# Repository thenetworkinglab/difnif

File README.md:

# DifNif: DBA-ESDI Solid State Drive Emulator

DifNif is a drive emulator that replaces an IBM DBA-ESDI hard drive. 
It was designed by Eric Schlaepfer ([schlae/difnif](https://github.com/schlae/difnif)),
with the project's initial release intended to replace the hard drive in 
IBM ThinkPad 700C laptops, also including an alpha version of a PS/2 desktop 
form-factor emulator.  This fork is an attempt to complete 
the development of the 72-pin board for PS/2 desktops; the changes are 
listed in [docs/formfactor-review.md](docs/formfactor-review.md).

And before you ask: the name 'DifNif' comes from DF9F, 
the Micro Channel adapter ID that IBM's DBA-ESDI drives report.

**Status:** the Rev P2 PS/2 board works in a PS/2 55SX and Model 70, with or
without a Teensy, booting DOS 6.22 and OS/2 1.1. Releases are listed in
[CHANGELOG.md](CHANGELOG.md).

## Background

IBM PS/2 computers from the late 1980s and early 1990s typically used a
disk interface called DBA-ESDI (Direct Bus Attach - Enhanced
Small Device Interface). A DBA-ESDI drive has its controller integrated
with the drive electronics, and sits directly on the Micro Channel
bus, more like an IDE drive, but with its own register interface.

These drives are becoming rare because many have failed mechanically or
been damaged by leaking capacitors. MCA SCSI cards are an alternative on some
machines, but are getting expensive and difficult to find as well and
aren't compatible with all PS/2s. Some PS/2s also need an IML (initial microcode load)
partition on their disk, and can only load it from a DBA-ESDI drive.

DifNif implements the DBA-ESDI interface in a Lattice iCE40 FPGA and keeps
the disk as an image file on an SD card. Eric's design pairs the FPGA with a
Teensy 4.1 microcontroller; this fork adds a build that runs a small RISC-V
processor inside the FPGA instead, so the board needs no Teensy.

## Status

The Rev P2 board for PS/2 desktops (this fork) can be built two ways from
the same board:

- **FPGA-only** (recommended): no Teensy; the SD card goes in the board's
  own socket. Release v2026.11.23-1.
- **With a Teensy 4.1**, Eric's arrangement, with this fork's fixes; the SD
  card goes in the Teensy. Firmware v2026.11.21-5 and FPGA v2026.11.21-1.

Both work in a PS/2 55SX and a Model 70: they're set up with the Reference
Diskette, boot DOS 6.22, and pass a copy test that checks every file written
(the FPGA-only build overnight in the Model 70: about 367 rounds, no errors).
OS/2 1.1 installs and boots with the Teensy build in both machines, and boots
with the FPGA-only build in the Model 70 (not yet tried in its 55SX). With
the FPGA-only build, switching the PS/2 off straight after a write loses
nothing.

Speed, measured with DiskMeter (random / sequential / buffered, KB/s) and
sunbench (raw BIOS reads and writes, 64 KB blocks, MB/s), in a Model 70
(8570-A21: 25 MHz 80386DX, 64 KB cache) and a 55SX (8555-061: 16 MHz
80386SX, no cache):

| | Model 70 | 55SX |
|---|---|---|
| FPGA-only, DiskMeter | 3555 / 3206 / 3213 | 2222 / 2241 / 2432 |
| FPGA-only, sunbench read / write | 2.99 / 2.50 | 2.13 / 1.87 |
| Teensy build, DiskMeter | 1942 / 2036 / 2010 | 2108 / 2266 / 2305 |
| Eric's original design, DiskMeter | about 990 | about 690 |
| McIDE (an IDE adapter), DiskMeter | 2477 / 2477 / 2477 | 1867 / 1876 / 2005 |

Not yet tested: the PS/2 50Z, and this fork's FPGA changes on the ThinkPad
board (Eric's ThinkPad board works with his original design, on the `main`
branch).

**Data loss:** this is a hobby project with no formal testing. Keep backup
copies of all disk images.

## Making a board

This needs surface-mount assembly (an assembly service will do it), a
computer with the open-source FPGA tools, and an FTDI FT232H adapter. These
steps are for the FPGA-only build; the Teensy build differs in steps 4 to 6
(see below).

1. **Order the board.** `pcb_formfactor/fab/` has the Gerber and drill files
   (`DifNifFormFactor-RevP2.zip`), a parts list and a placement file for an
   assembly service. Order it 1.6 mm thick, with gold fingers and a bevelled
   connector edge; [docs/formfactor-review.md](docs/formfactor-review.md),
   "Fab files", has the details. Fit the 2x4 header J2 yourself (for
   programming); the Teensy socket is only needed for the Teensy build.
2. **Print the sled.** [mech/difnif_PS2_drive_sled.STL](mech/difnif_PS2_drive_sled.STL)
   replaces the IBM drive's sled; the board screws into it.
3. **Install the tools:** yosys, nextpnr and icestorm (for example
   [oss-cad-suite](https://github.com/YosysHQ/oss-cad-suite-build)), and a
   RISC-V C compiler, `riscv64-elf-gcc` (for example from Homebrew).
4. **Build and program the FPGA.** In `verilog/`:

       make BOARD=ps2 CPU=1          # firmware and FPGA, into build/ps2-cpu/
       make prog BOARD=ps2 CPU=1     # writes the FPGA's flash through J2

   Wire the FT232H to J2:

   | J2 pin | Signal | FT232H pin |
   |---|---|---|
   | 1 | Flash chip select | AD4 |
   | 2 | CDONE | AD6 |
   | 3 | SCK | AD0 |
   | 4 | CRESET | AD7 |
   | 5 | Flash data out (CIPO) | AD2 |
   | 6 | GND | GND |
   | 7 | Flash data in (COPI) | AD1 |
   | 8 | +3.3 V (leave unconnected) | |

   The board must be powered while it's programmed: in a switched-on PS/2,
   or on the bench with 5 V on the Teensy socket's VIN pin (U13 pin 48).
5. **Make the disk image.** The drive is a file called `disk0.img`, a whole
   number of megabytes up to 1023 MB, in the root directory of a FAT32 or
   exFAT SD card. For 120 MB:

       dd if=/dev/zero of=disk0.img bs=1048576 count=120

   The file may be in up to 32 pieces on the card. The card goes in the
   board's socket, J3. [docs/sd-card.md](docs/sd-card.md) has the steps for
   putting an image on a card (erase it, then copy, so the image is in one
   piece) and what the log means if the board can't use it.
6. **Optional: the serial log.** The board reports what it found on the card
   (and why, if it can't use the image) on a 1 Mbaud, 8N1 serial line at the
   Teensy socket: it sends on the pin where a Teensy 4.1's pin 16 would go,
   and listens on pin 17's. Use a 3.3 V USB-serial adapter (never RS-232
   levels): the FT232H when it isn't programming (AD1 to pin 16, AD0 to pin
   17, and GND), or a Teensy running
   [fw/teensy_log/teensy_log.ino](fw/teensy_log/teensy_log.ino). Any key
   prints the summary again; `v` traces every command; `p` changes the bus
   release time after another device's -PREEMPT (6 us by default).
7. **Fit it in the PS/2.** In the Model 70, check the orientation first: its
   drive socket isn't keyed, and the board fitted upside down puts +12 V on
   signal pins. The component side (where `A01` is printed) faces the same way
   as the side of the IBM drive's board that faces the drive casing. The 55SX
   socket is keyed. The first start gives error 165 (configuration changed):
   run the Reference Diskette's automatic configuration. Then let it create
   the reference partition if the machine needs one, and install DOS or OS/2
   as on a new drive.
8. **Check it.** [tools/copytest](tools/copytest/) copies test files back
   and forth under DOS (`TEST.BAT`, or `FOREVER.BAT` overnight), and
   `copytest.py check` verifies every copy by reading `disk0.img` on another
   computer afterwards.

## The Teensy build

The same board with a Teensy 4.1 in its socket: Eric's arrangement, with
the SD card in the Teensy's slot instead of J3. This fork fixed a good deal
of it along the way ([docs/formfactor-review.md](docs/formfactor-review.md)
has each finding, [CHANGELOG.md](CHANGELOG.md) each release):

- **The board (Rev P2):** the reset input, which floated and was the likely
  cause of Eric's Rev P1 board failing in a 50Z; level shifters that had
  5 V on a pin rated for 4.6 V; the missing key slot in the edge connector;
  the -CD SFDBK signal, which wasn't driven.
- **The FPGA design:** write data latched too early to work at IBM's timing
  limits; the POS
  registers (the card's adapter ID); 8-bit reads that the Model 70 read
  wrongly; the PS/2's channel reset, which didn't reset the card; DMA
  requests that dropped too late; DMA left enabled at terminal count, which
  hung OS/2 1.1 at its second disk read.
- **The Teensy firmware:** the last write before the PS/2 is switched off
  could be lost; status words OS/2 left unread were still waiting at its
  next command; the answer to OS/2's probe for a second drive.
- **Speed:** a sector buffer and burst DMA in the FPGA took DiskMeter from
  about 690-990 KB/s with Eric's design to about 2 MB/s.

To build it:

- Load [difnift/difnift.ino](difnift/difnift.ino) with the Arduino IDE and
  PJRC's Teensy support (Teensy 4.1).
- Build the FPGA with `make BOARD=ps2` and program it with
  `make prog BOARD=ps2` (the Teensy's USB powers the board on the bench).
- [difbench/difbench.ino](difbench/difbench.ino) tests the Teensy-to-FPGA
  link on the bench, before the board goes in a PS/2.
- [docs/formfactor-review.md](docs/formfactor-review.md), "Bring-up", takes
  a new board from first power to a PS/2 one step at a time.

## What's in the repository

| | |
|---|---|
| [pcb_formfactor/](pcb_formfactor/) | the PS/2 board (KiCad), with fab files in `fab/` |
| [verilog/](verilog/) | the FPGA design: `mcabus.v` (the Micro Channel interface and ESDI registers), `sectorbuf.v`, and for the FPGA-only build `soc.v` (the processor), `sdhost.v` and `sdbridge.v` (the SD card); `teensy.v` for the Teensy build |
| [fw/](fw/) | the FPGA-only build's firmware (C, RISC-V) |
| [difnift/](difnift/) | the Teensy build's firmware |
| [tools/](tools/) | `timing_budget.py` (checks the design against IBM's bus timing), `copytest/`, and board-checking scripts |
| [mech/](mech/) | 3D-printed sled and carriers |
| [pcb_thinkpad/](pcb_thinkpad/) | Eric's ThinkPad 700C board |
| [docs/](docs/) | the design notes below |

The simulations: in `verilog/`, `./run_sim72.sh` runs a model of the PS/2's
bus against the design at IBM's timing limits (`./run_sim72.sh cpu` for the
FPGA-only build, with its firmware and an SD card model), and
`./run_sdsim.sh` and `./run_socsim.sh` test the SD controller and the
processor's start-up. They need Icarus Verilog.

## Design notes

- [docs/fpga-only.md](docs/fpga-only.md): the FPGA-only build, how it works
  and how it was tested and tuned.
- [docs/formfactor-review.md](docs/formfactor-review.md): the review of
  Eric's Rev P1 board, the Rev P2 changes, bring-up, and the speed work on
  the Teensy build.
- [docs/sd-card.md](docs/sd-card.md): preparing the SD card, backing up
  an image, and what the start-up log means when the card or image can't
  be used.
- [docs/os2.md](docs/os2.md): what it took to boot OS/2 1.1.
- [docs/verify-findings.md](docs/verify-findings.md): how to check each
  finding against Eric's files and IBM's documents.
- [docs/rev-p3-spec.md](docs/rev-p3-spec.md): a draft specification for
  the next board: FPGA-only, USB-C, full-size SD socket.

## Reference documents

- [IBM DBA-ESDI reference](https://ardent-tool.com/docs/pdf/j_mcspec.pdf)
- [DBA-ESDI 72-pin connector pinout](https://ardent-tool.com/storage/DBA_ESDI.html)
- [IBM PS/2 Hardware Interface Technical Reference, Micro Channel chapter](https://ardent-tool.com/docs/pdf/ps2_50-60_techref_ch2_microchannel_architecture.pdf)

## License

Designed by Eric Schlaepfer; modified in this fork by thenetworkinglab (2026).
Licensed under the
[CERN Open Hardware Licence Version 2 - Strongly Reciprocal](https://ohwr.org/cern_ohl_s_v2.txt).

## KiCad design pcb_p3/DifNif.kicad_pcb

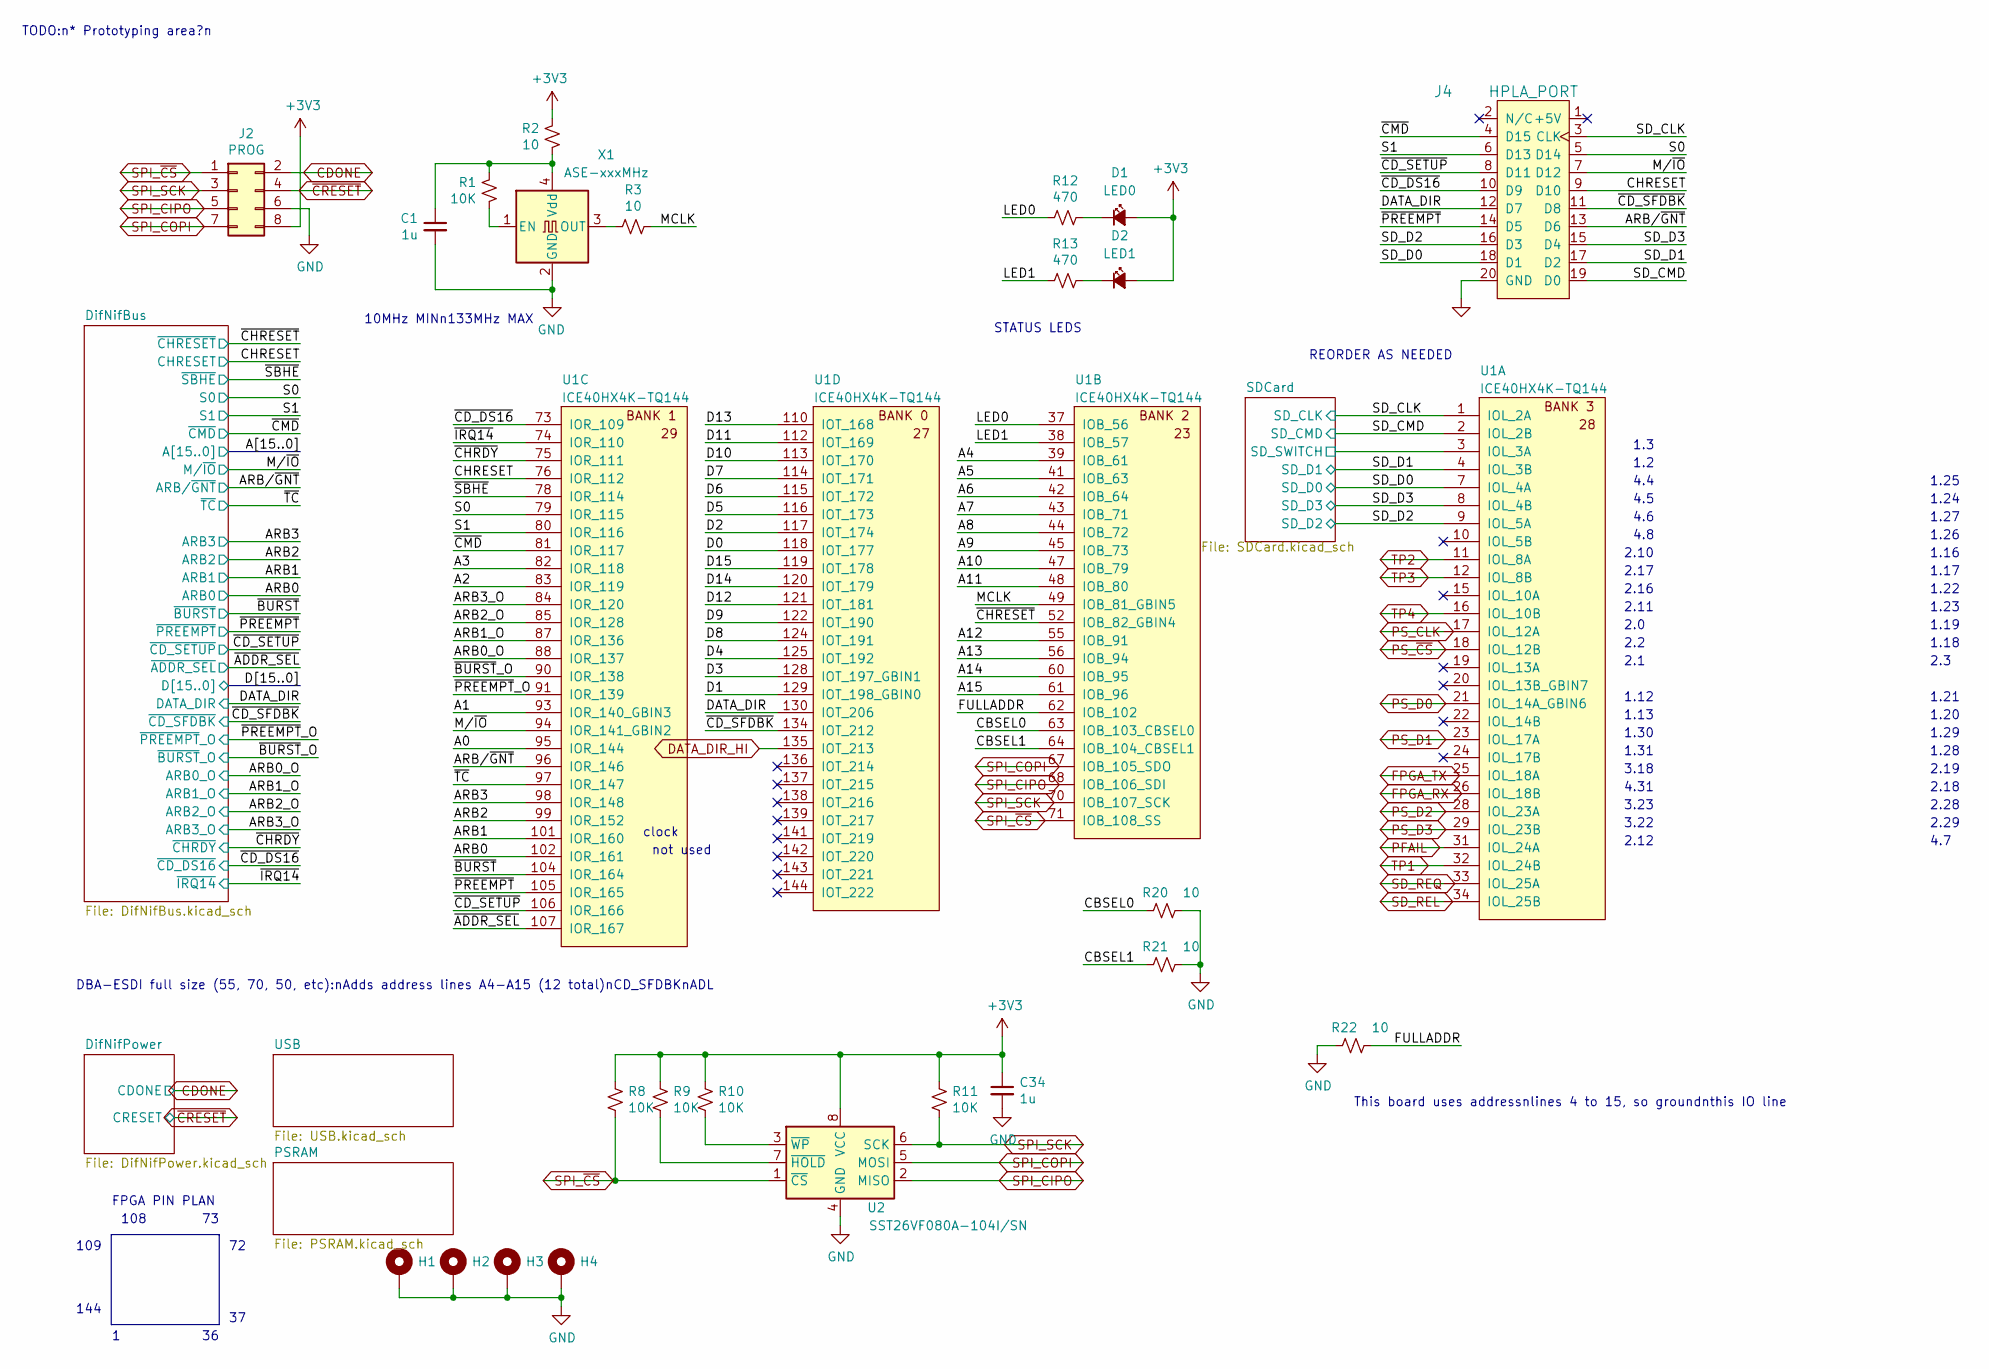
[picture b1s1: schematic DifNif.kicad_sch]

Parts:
C1, C34: 1u; CAPC1608X100; Mouser 810-CGA3E1X7R1C105AC
D1: LED0; LEDM1608X50
D2: LED1; LEDM1608X50
H1, H2, H3, H4: MountingHole_Pad; MountingHole_2.7mm_Pad
J2: PROG; PinHeader_2x04_P2.54mm_Vertical
J4: HPLA_PORT; PinHeader_2x10_P2.54mm_Vertical
R1, R8, R9, R10, R11: 10K; RESC1608X55; Mouser 603-RC0603FR-0710KL
R2, R3, R20, R21, R22: 10; RESC1608X55; Mouser 603-RC0603FR-0710RL
R12, R13: 470; RESC1608X55; Mouser 603-RC0603FR-07470RL
U1: ICE40HX4K-TQ144; TSQFP50P2200X2200X160-144; Mouser 842-ICE40HX4K-TQ144
U2: SST26VF080A-104I/SN; SOP127P620X175-8; Mouser 579-26VF080A-104I/SN
X1: ASE-xxxMHz; XTAL320X250X120-4; Mouser 520-ECS-2333-100-BNT

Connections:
+3V3: C34.1, D1.2 (A), D2.2 (A), J2.8, R2.1, R8.1, R9.1, R10.1, R11.1, U2.8 (VCC); also elsewhere on the board
/A0: U1.95 (IOR_144); also elsewhere on the board
/A1: U1.93 (IOR_140_GBIN3); also elsewhere on the board
/A2: U1.83 (IOR_119); also elsewhere on the board
/A3: U1.82 (IOR_118); also elsewhere on the board
/A4: U1.39 (IOB_61); also elsewhere on the board
/A5: U1.41 (IOB_63); also elsewhere on the board
/A6: U1.42 (IOB_64); also elsewhere on the board
/A7: U1.43 (IOB_71); also elsewhere on the board
/A8: U1.44 (IOB_72); also elsewhere on the board
/A9: U1.45 (IOB_73); also elsewhere on the board
/A10: U1.47 (IOB_79); also elsewhere on the board
/A11: U1.48 (IOB_80); also elsewhere on the board
/A12: U1.55 (IOB_91); also elsewhere on the board
/A13: U1.56 (IOB_94); also elsewhere on the board
/A14: U1.60 (IOB_95); also elsewhere on the board
/A15: U1.61 (IOB_96); also elsewhere on the board
/ARB0: U1.102 (IOR_161); also elsewhere on the board
/ARB0_O: U1.88 (IOR_137); also elsewhere on the board
/ARB1: U1.101 (IOR_160); also elsewhere on the board
/ARB1_O: U1.87 (IOR_136); also elsewhere on the board
/ARB2: U1.99 (IOR_152); also elsewhere on the board
/ARB2_O: U1.85 (IOR_128); also elsewhere on the board
/ARB3: U1.98 (IOR_148); also elsewhere on the board
/ARB3_O: U1.84 (IOR_120); also elsewhere on the board
/ARB/~GNT: J4.13 (D6), U1.96 (IOR_146); also elsewhere on the board
/CBSEL0: R20.2, U1.63 (IOB_103_CBSEL0)
/CBSEL1: R21.2, U1.64 (IOB_104_CBSEL1)
/CHRESET: J4.9 (D10), U1.76 (IOR_112); also elsewhere on the board
/D0: U1.118 (IOT_177); also elsewhere on the board
/D1: U1.129 (IOT_198_GBIN0); also elsewhere on the board
/D2: U1.117 (IOT_174); also elsewhere on the board
/D3: U1.128 (IOT_197_GBIN1); also elsewhere on the board
/D4: U1.125 (IOT_192); also elsewhere on the board
/D5: U1.116 (IOT_173); also elsewhere on the board
/D6: U1.115 (IOT_172); also elsewhere on the board
/D7: U1.114 (IOT_171); also elsewhere on the board
/D8: U1.124 (IOT_191); also elsewhere on the board
/D9: U1.122 (IOT_190); also elsewhere on the board
/D10: U1.113 (IOT_170); also elsewhere on the board
/D11: U1.112 (IOT_169); also elsewhere on the board
/D12: U1.121 (IOT_181); also elsewhere on the board
/D13: U1.110 (IOT_168); also elsewhere on the board
/D14: U1.120 (IOT_179); also elsewhere on the board
/D15: U1.119 (IOT_178); also elsewhere on the board
/DATA_DIR: J4.12 (D7), U1.130 (IOT_206); also elsewhere on the board
/FULLADDR: R22.1, U1.62 (IOB_102)
/LED0: R12.2, U1.37 (IOB_56)
/LED1: R13.2, U1.38 (IOB_57)
/MCLK: R3.1, U1.49 (IOB_81_GBIN5)
/M/~IO: J4.7 (D12), U1.94 (IOR_141_GBIN2); also elsewhere on the board
/S0: J4.5 (D14), U1.79 (IOR_115); also elsewhere on the board
/S1: J4.6 (D13), U1.80 (IOR_116); also elsewhere on the board
/SD_CLK: J4.3 (CLK), U1.1 (IOL_2A); also elsewhere on the board
/SD_CMD: J4.19 (D0), U1.2 (IOL_2B); also elsewhere on the board
/SD_D0: J4.18 (D1), U1.7 (IOL_4A); also elsewhere on the board
/SD_D1: J4.17 (D2), U1.4 (IOL_3B); also elsewhere on the board
/SD_D2: J4.16 (D3), U1.9 (IOL_5A); also elsewhere on the board
/SD_D3: J4.15 (D4), U1.8 (IOL_4B); also elsewhere on the board
/~ADDR_SEL: U1.107 (IOR_167)
/~BURST: U1.104 (IOR_164); also elsewhere on the board
/~BURST_O: U1.90 (IOR_138); also elsewhere on the board
/~CD_DS16: J4.10 (D9), U1.73 (IOR_109); also elsewhere on the board
/~CD_SETUP: J4.8 (D11), U1.106 (IOR_166); also elsewhere on the board
/~CD_SFDBK: J4.11 (D8), U1.134 (IOT_212); also elsewhere on the board
/~CHRDY: U1.75 (IOR_111); also elsewhere on the board
/~CHRESET: U1.52 (IOB_82_GBIN4); also elsewhere on the board
/~CMD: J4.4 (D15), U1.81 (IOR_117); also elsewhere on the board
/~IRQ14: U1.74 (IOR_110); also elsewhere on the board
/~PREEMPT: J4.14 (D5), U1.105 (IOR_165); also elsewhere on the board
/~PREEMPT_O: U1.91 (IOR_139); also elsewhere on the board
/~SBHE: U1.78 (IOR_114); also elsewhere on the board
/~TC: U1.97 (IOR_147); also elsewhere on the board
CDONE: J2.2; also elsewhere on the board
DATA_DIR_HI: U1.135 (IOT_213); also elsewhere on the board
FPGA_RX: U1.26 (IOL_18B); also elsewhere on the board
FPGA_TX: U1.25 (IOL_18A); also elsewhere on the board
GND: C1.2, C34.2, H1.1, H2.1, H3.1, H4.1, J2.6, J4.20 (GND), R20.1, R21.1, R22.2, U2.4 (GND), X1.2 (GND); also elsewhere on the board
unnamed: D1.1 (K), R12.1
unnamed: D2.1 (K), R13.1
unnamed: R9.2, U2.7 (~HOLD)
unnamed: R10.2, U2.3 (~WP)
unnamed: R1.2, X1.1 (EN)
unnamed: R3.2, X1.3 (OUT)
unnamed: C1.1, R1.1, R2.2, X1.4 (Vdd)
PFAIL: U1.31 (IOL_24A); also elsewhere on the board
PS_CLK: U1.17 (IOL_12A); also elsewhere on the board
PS_D0: U1.21 (IOL_14A_GBIN6); also elsewhere on the board
PS_D1: U1.23 (IOL_17A); also elsewhere on the board
PS_D2: U1.28 (IOL_23A); also elsewhere on the board
PS_D3: U1.29 (IOL_23B); also elsewhere on the board
PS_~CS: U1.18 (IOL_12B); also elsewhere on the board
SD_CD: U1.3 (IOL_3A); also elsewhere on the board
SD_REL: U1.34 (IOL_25B); also elsewhere on the board
SD_REQ: U1.33 (IOL_25A); also elsewhere on the board
SPI_CIPO: J2.5, U1.68 (IOB_106_SDI), U2.2 (MISO); also elsewhere on the board
SPI_COPI: J2.7, U1.67 (IOB_105_SDO), U2.5 (MOSI); also elsewhere on the board
SPI_SCK: J2.3, R11.2, U1.70 (IOB_107_SCK), U2.6 (SCK); also elsewhere on the board
SPI_~CS: J2.1, R8.2, U1.71 (IOB_108_SS), U2.1 (~CS); also elsewhere on the board
TP1: U1.32 (IOL_24B); also elsewhere on the board
TP2: U1.11 (IOL_8A); also elsewhere on the board
TP3: U1.12 (IOL_8B); also elsewhere on the board
TP4: U1.16 (IOL_10B); also elsewhere on the board
~CRESET: J2.4; also elsewhere on the board

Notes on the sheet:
2.1
2.19
4.31
1.16
2.17
2.18
1.30
2.16
1.27
clock
1.2
REORDER AS NEEDED
2.3
2.0
3.22
STATUS LEDS
TODO:n* Prototyping area?n
4.7
1.31
1.21
2.28
1.24
1.29
1.19
4.6
2.12
2.10
3.18
1.17
3.23
1.3
1.25
4.5
1.20
2.29
2.11
4.4
1.18
1.28
2.2

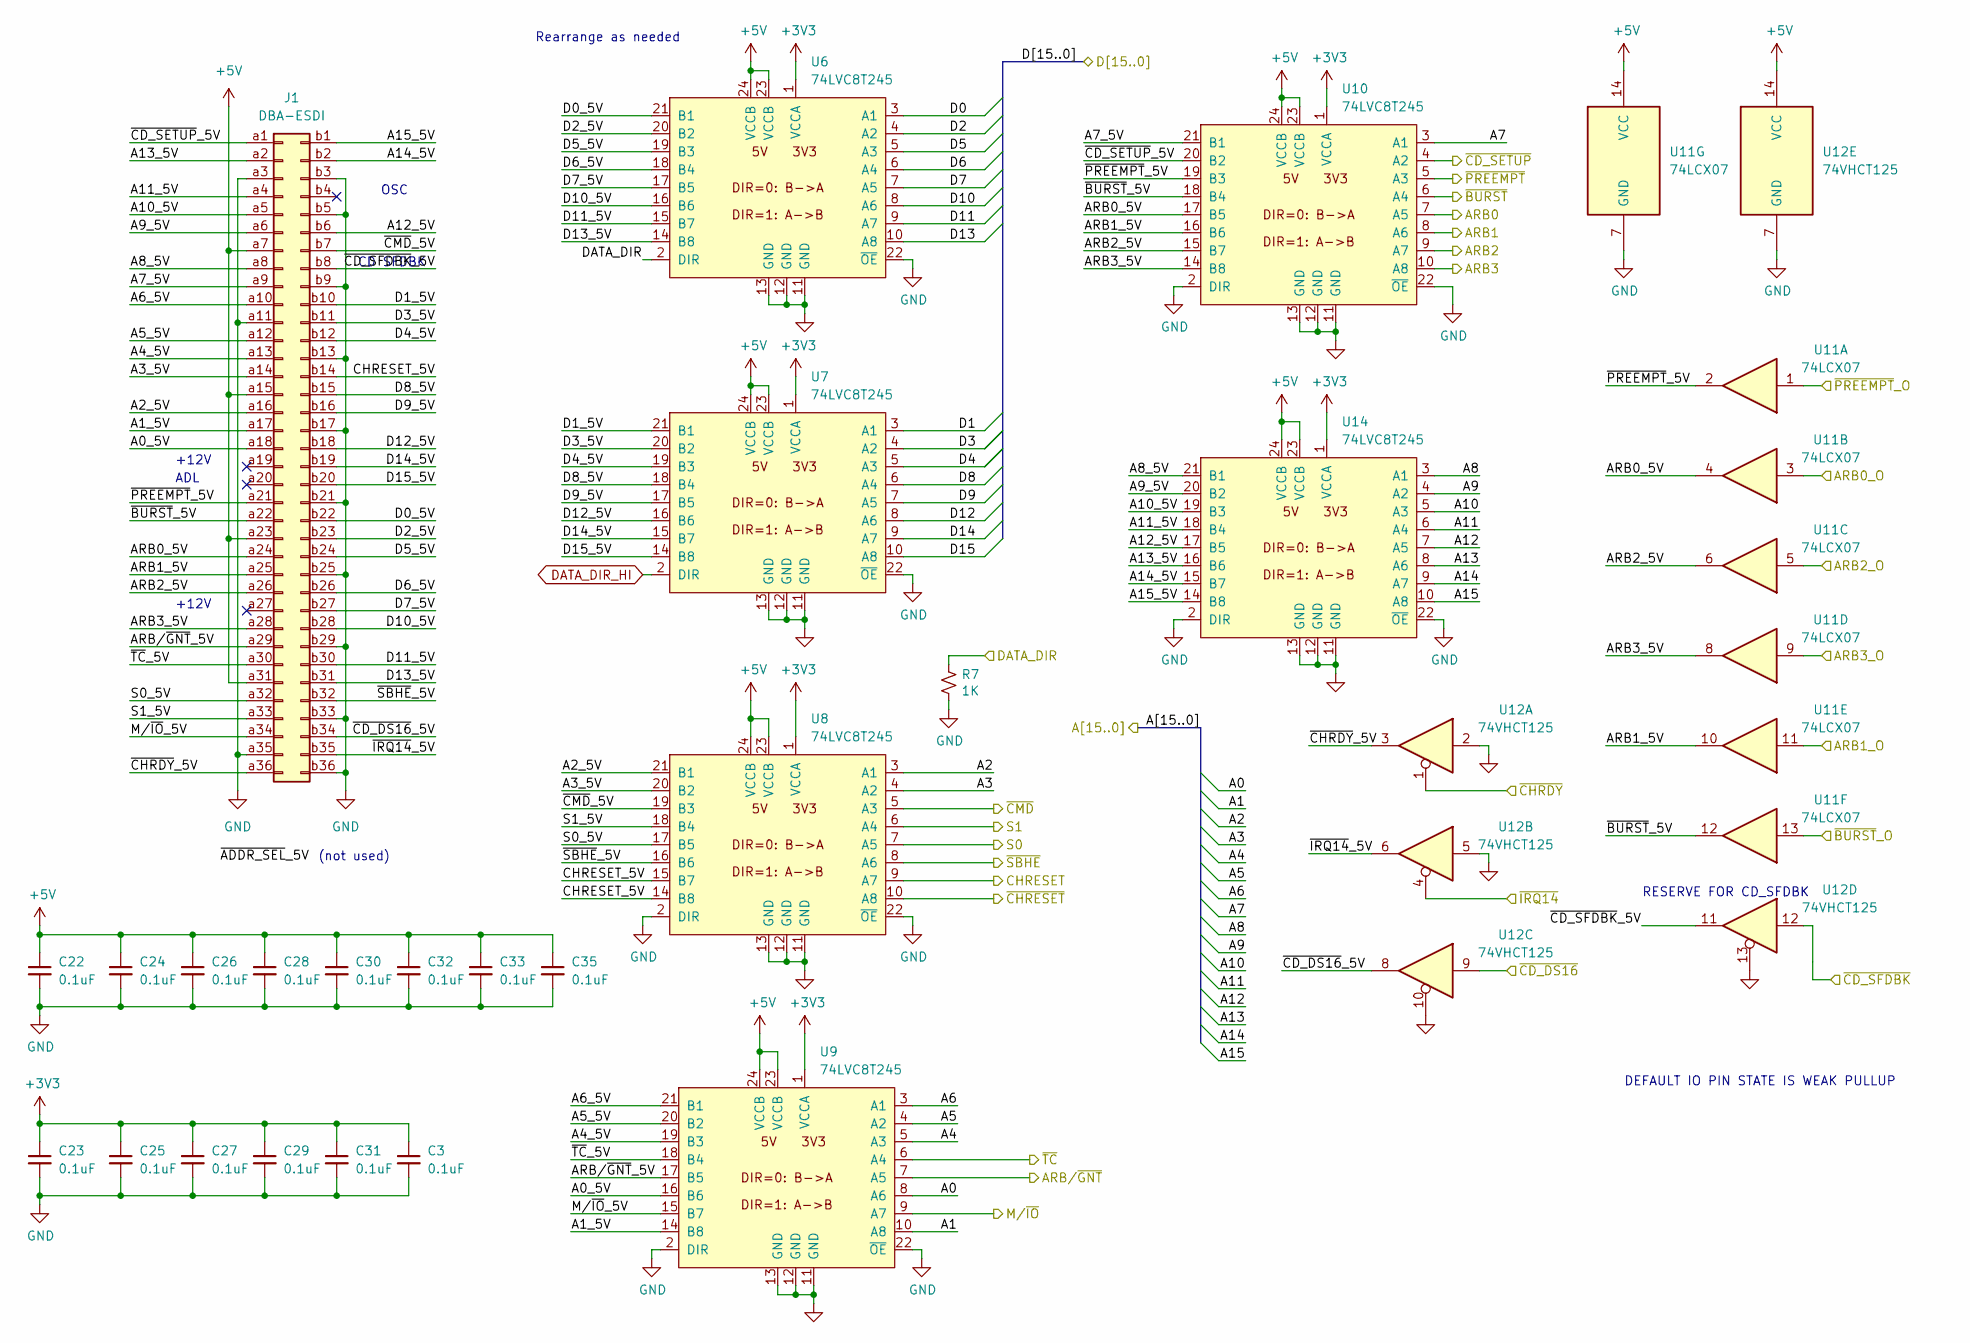
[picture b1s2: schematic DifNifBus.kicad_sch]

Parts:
C3, C22, C23, C24, C25, C26, C27, C28, C29, C30, C31, C32, C33, C35: 0.1uF; CAPC1608X100
J1: DBA-ESDI; BUS_DBA_ESDI
R7: 1K; RESC1608X55; Mouser 603-RC0603FR-071KL
U6, U7, U8, U9, U10, U14: 74LVC8T245; TSOP65P640X120-24; Mouser 595-SN74LVC8T245PWR
U11: 74LCX07; TSOP65P640X110-14; Mouser 757-74LCX07FTAE
U12: 74VHCT125; TSOP65P640X110-14; Mouser 757-74VHCT125AFT

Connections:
+3V3: C3.1, C23.1, C25.1, C27.1, C29.1, C31.1, U6.1 (VCCA), U7.1 (VCCA), U8.1 (VCCA), U9.1 (VCCA), U10.1 (VCCA), U14.1 (VCCA); also elsewhere on the board
+5V: C22.1, C24.1, C26.1, C28.1, C30.1, C32.1, C33.1, C35.1, J1.a7, J1.a15, J1.a23, J1.a31, U6.23 (VCCB), U6.24 (VCCB), U7.23 (VCCB), U7.24 (VCCB), U8.23 (VCCB), U8.24 (VCCB), U9.23 (VCCB), U9.24 (VCCB), U10.23 (VCCB), U10.24 (VCCB), U11.14 (VCC), U12.14 (VCC), U14.23 (VCCB), U14.24 (VCCB); also elsewhere on the board
/A0: U9.8 (A5); also elsewhere on the board
/A1: U9.10 (A7); also elsewhere on the board
/A2: U8.3 (A0); also elsewhere on the board
/A3: U8.4 (A1); also elsewhere on the board
/A4: U9.5 (A2); also elsewhere on the board
/A5: U9.4 (A1); also elsewhere on the board
/A6: U9.3 (A0); also elsewhere on the board
/A7: U10.3 (A0); also elsewhere on the board
/A8: U14.3 (A0); also elsewhere on the board
/A9: U14.4 (A1); also elsewhere on the board
/A10: U14.5 (A2); also elsewhere on the board
/A11: U14.6 (A3); also elsewhere on the board
/A12: U14.7 (A4); also elsewhere on the board
/A13: U14.8 (A5); also elsewhere on the board
/A14: U14.9 (A6); also elsewhere on the board
/A15: U14.10 (A7); also elsewhere on the board
/ARB0: U10.7 (A4); also elsewhere on the board
/ARB0_O: U11.3; also elsewhere on the board
/ARB1: U10.8 (A5); also elsewhere on the board
/ARB1_O: U11.11; also elsewhere on the board
/ARB2: U10.9 (A6); also elsewhere on the board
/ARB2_O: U11.5; also elsewhere on the board
/ARB3: U10.10 (A7); also elsewhere on the board
/ARB3_O: U11.9; also elsewhere on the board
/ARB/~GNT: U9.7 (A4); also elsewhere on the board
/CHRESET: U8.9 (A6); also elsewhere on the board
/D0: U6.3 (A0); also elsewhere on the board
/D1: U7.3 (A0); also elsewhere on the board
/D2: U6.4 (A1); also elsewhere on the board
/D3: U7.4 (A1); also elsewhere on the board
/D4: U7.5 (A2); also elsewhere on the board
/D5: U6.5 (A2); also elsewhere on the board
/D6: U6.6 (A3); also elsewhere on the board
/D7: U6.7 (A4); also elsewhere on the board
/D8: U7.6 (A3); also elsewhere on the board
/D9: U7.7 (A4); also elsewhere on the board
/D10: U6.8 (A5); also elsewhere on the board
/D11: U6.9 (A6); also elsewhere on the board
/D12: U7.8 (A5); also elsewhere on the board
/D13: U6.10 (A7); also elsewhere on the board
/D14: U7.9 (A6); also elsewhere on the board
/D15: U7.10 (A7); also elsewhere on the board
/DATA_DIR: R7.1, U6.2 (DIR); also elsewhere on the board
/DifNifBus/A0_5V: J1.a18, U9.16 (B5)
/DifNifBus/A1_5V: J1.a17, U9.14 (B7)
/DifNifBus/A2_5V: J1.a16, U8.21 (B0)
/DifNifBus/A3_5V: J1.a14, U8.20 (B1)
/DifNifBus/A4_5V: J1.a13, U9.19 (B2)
/DifNifBus/A5_5V: J1.a12, U9.20 (B1)
/DifNifBus/A6_5V: J1.a10, U9.21 (B0)
/DifNifBus/A7_5V: J1.a9, U10.21 (B0)
/DifNifBus/A8_5V: J1.a8, U14.21 (B0)
/DifNifBus/A9_5V: J1.a6, U14.20 (B1)
/DifNifBus/A10_5V: J1.a5, U14.19 (B2)
/DifNifBus/A11_5V: J1.a4, U14.18 (B3)
/DifNifBus/A12_5V: J1.b6, U14.17 (B4)
/DifNifBus/A13_5V: J1.a2, U14.16 (B5)
/DifNifBus/A14_5V: J1.b2, U14.15 (B6)
/DifNifBus/A15_5V: J1.b1, U14.14 (B7)
/DifNifBus/ARB0_5V: J1.a24, U10.17 (B4), U11.4
/DifNifBus/ARB1_5V: J1.a25, U10.16 (B5), U11.10
/DifNifBus/ARB2_5V: J1.a26, U10.15 (B6), U11.6
/DifNifBus/ARB3_5V: J1.a28, U10.14 (B7), U11.8
/DifNifBus/ARB/~GNT_5V: J1.a29, U9.17 (B4)
/DifNifBus/CHRESET_5V: J1.b14, U8.14 (B7), U8.15 (B6)
/DifNifBus/D0_5V: J1.b22, U6.21 (B0)
/DifNifBus/D1_5V: J1.b10, U7.21 (B0)
/DifNifBus/D2_5V: J1.b23, U6.20 (B1)
/DifNifBus/D3_5V: J1.b11, U7.20 (B1)
/DifNifBus/D4_5V: J1.b12, U7.19 (B2)
/DifNifBus/D5_5V: J1.b24, U6.19 (B2)
/DifNifBus/D6_5V: J1.b26, U6.18 (B3)
/DifNifBus/D7_5V: J1.b27, U6.17 (B4)
/DifNifBus/D8_5V: J1.b15, U7.18 (B3)
/DifNifBus/D9_5V: J1.b16, U7.17 (B4)
/DifNifBus/D10_5V: J1.b28, U6.16 (B5)
/DifNifBus/D11_5V: J1.b30, U6.15 (B6)
/DifNifBus/D12_5V: J1.b18, U7.16 (B5)
/DifNifBus/D13_5V: J1.b31, U6.14 (B7)
/DifNifBus/D14_5V: J1.b19, U7.15 (B6)
/DifNifBus/D15_5V: J1.b20, U7.14 (B7)
/DifNifBus/M/~IO_5V: J1.a34, U9.15 (B6)
/DifNifBus/S0_5V: J1.a32, U8.17 (B4)
/DifNifBus/S1_5V: J1.a33, U8.18 (B3)
/DifNifBus/~BURST_5V: J1.a22, U10.18 (B3), U11.12
/DifNifBus/~CD_DS16_5V: J1.b34, U12.8
/DifNifBus/~CD_SETUP_5V: J1.a1, U10.20 (B1)
/DifNifBus/~CD_SFDBK_5V: J1.b8, U12.11
/DifNifBus/~CHRDY_5V: J1.a36, U12.3
/DifNifBus/~CMD_5V: J1.b7, U8.19 (B2)
/DifNifBus/~IRQ14_5V: J1.b35, U12.6
/DifNifBus/~PREEMPT_5V: J1.a21, U10.19 (B2), U11.2
/DifNifBus/~SBHE_5V: J1.b32, U8.16 (B5)
/DifNifBus/~TC_5V: J1.a30, U9.18 (B3)
/M/~IO: U9.9 (A6); also elsewhere on the board
/S0: U8.7 (A4); also elsewhere on the board
/S1: U8.6 (A3); also elsewhere on the board
/~BURST: U10.6 (A3); also elsewhere on the board
/~BURST_O: U11.13; also elsewhere on the board
/~CD_DS16: U12.9; also elsewhere on the board
/~CD_SETUP: U10.4 (A1); also elsewhere on the board
/~CD_SFDBK: U12.12; also elsewhere on the board
/~CHRDY: U12.1; also elsewhere on the board
/~CHRESET: U8.10 (A7); also elsewhere on the board
/~CMD: U8.5 (A2); also elsewhere on the board
/~IRQ14: U12.4; also elsewhere on the board
/~PREEMPT: U10.5 (A2); also elsewhere on the board
/~PREEMPT_O: U11.1; also elsewhere on the board
/~SBHE: U8.8 (A5); also elsewhere on the board
/~TC: U9.6 (A3); also elsewhere on the board
DATA_DIR_HI: U7.2 (DIR); also elsewhere on the board
GND: C3.2, C22.2, C23.2, C24.2, C25.2, C26.2, C27.2, C28.2, C29.2, C30.2, C31.2, C32.2, C33.2, C35.2, J1.a3, J1.a11, J1.a35, J1.b3, J1.b5, J1.b9, J1.b13, J1.b17, J1.b21, J1.b25, J1.b29, J1.b33, J1.b36, R7.2, U6.11 (GND), U6.12 (GND), U6.13 (GND), U6.22 (~OE), U7.11 (GND), U7.12 (GND), U7.13 (GND), U7.22 (~OE), U8.2 (DIR), U8.11 (GND), U8.12 (GND), U8.13 (GND), U8.22 (~OE), U9.2 (DIR), U9.11 (GND), U9.12 (GND), U9.13 (GND), U9.22 (~OE), U10.2 (DIR), U10.11 (GND), U10.12 (GND), U10.13 (GND), U10.22 (~OE), U11.7 (GND), U12.2, U12.5, U12.7 (GND), U12.10, U12.13, U14.2 (DIR), U14.11 (GND), U14.12 (GND), U14.13 (GND), U14.22 (~OE); also elsewhere on the board

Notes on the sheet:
Rearrange as needed
RESERVE FOR CD_SFDBK
+12V
(not used)
ADL
DEFAULT IO PIN STATE IS WEAK PULLUP
OSC
CD SFDBK

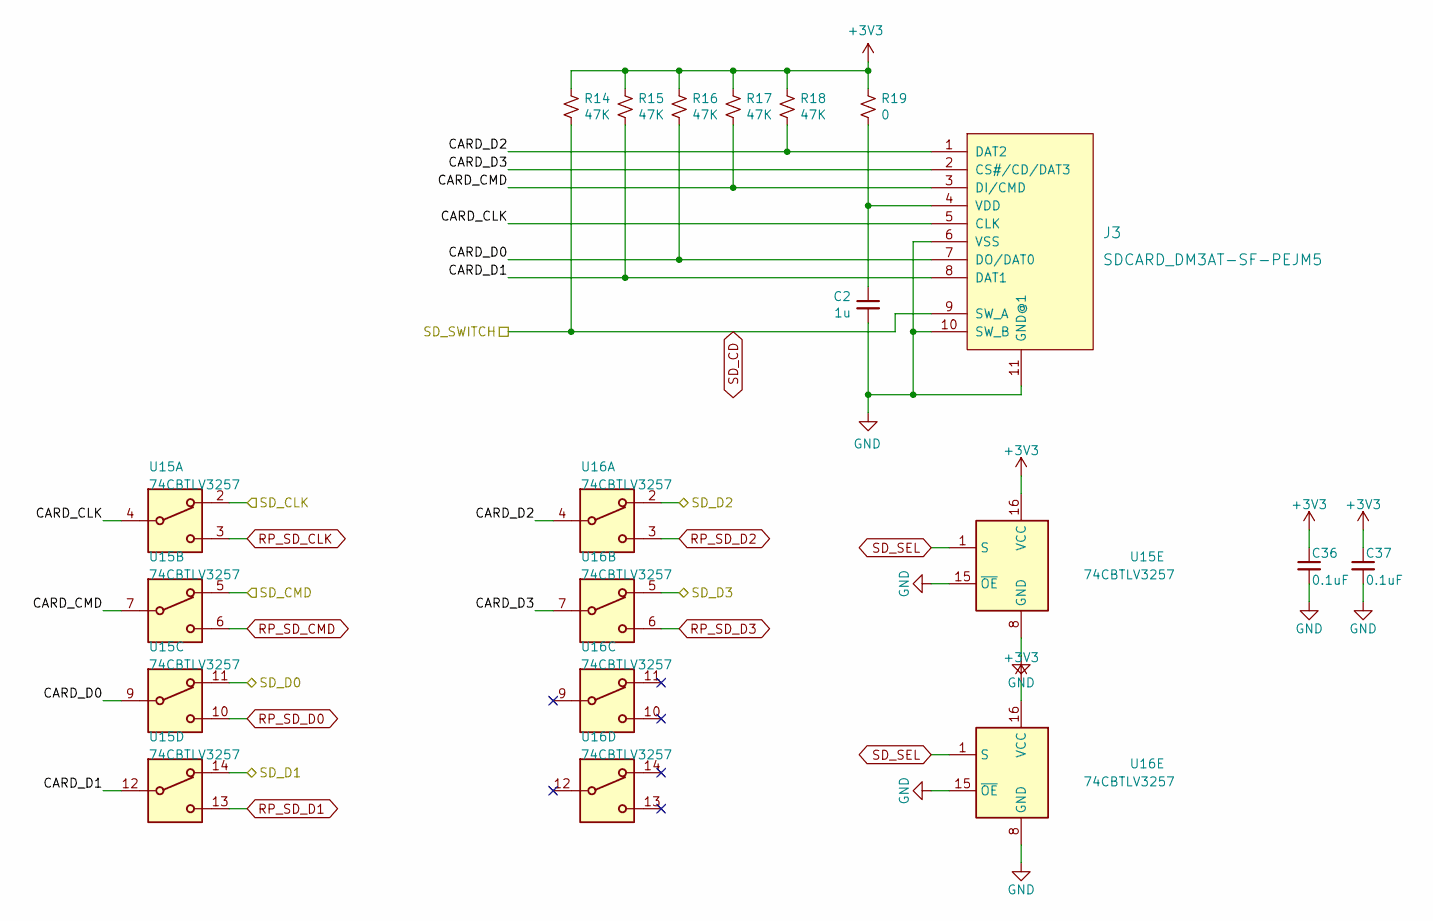
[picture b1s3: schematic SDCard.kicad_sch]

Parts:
C2: 1u; CAPC1608X100; Mouser 810-CGA3E1X7R1C105AC
C36, C37: 0.1uF; C_0603_1608Metric
J3: SDCARD_DM3AT-SF-PEJM5; microSD_HC_Hirose_DM3AT-SF-PEJM5; Mouser 798-DM3AT-SF-PEJM540
R14, R15, R16, R17, R18: 47K; RESC1608X55; Mouser 603-RC0603FR-0747KL
R19: 0; RESC2012X55; Mouser 603-RC0805FR-070RL
U15, U16: 74CBTLV3257; TSSOP-16_4.4x5mm_P0.65mm; MPN SN74CBTLV3257PWR

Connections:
+3V3: C36.1, C37.1, R14.1, R15.1, R16.1, R17.1, R18.1, R19.1, U15.16 (VCC), U16.16 (VCC); also elsewhere on the board
/SDCard/CARD_CLK: J3.5 (CLK), U15.4
/SDCard/CARD_CMD: J3.3 (DI/CMD), R17.2, U15.7
/SDCard/CARD_D0: J3.7 (DO/DAT0), R16.2, U15.9
/SDCard/CARD_D1: J3.8 (DAT1), R15.2, U15.12
/SDCard/CARD_D2: J3.1 (DAT2), R18.2, U16.4
/SDCard/CARD_D3: J3.2 (CS#/CD/DAT3), U16.7
/SD_CLK: U15.2; also elsewhere on the board
/SD_CMD: U15.5; also elsewhere on the board
/SD_D0: U15.11; also elsewhere on the board
/SD_D1: U15.14; also elsewhere on the board
/SD_D2: U16.2; also elsewhere on the board
/SD_D3: U16.5; also elsewhere on the board
GND: C2.2, C36.2, C37.2, J3.6 (VSS), J3.10 (SW_B), J3.11 (GND@1), U15.8 (GND), U15.15 (~OE), U16.8 (GND), U16.15 (~OE); also elsewhere on the board
unnamed: C2.1, J3.4 (VDD), R19.2
RP_SD_CLK: U15.3; also elsewhere on the board
RP_SD_CMD: U15.6; also elsewhere on the board
RP_SD_D0: U15.10; also elsewhere on the board
RP_SD_D1: U15.13; also elsewhere on the board
RP_SD_D2: U16.3; also elsewhere on the board
RP_SD_D3: U16.6; also elsewhere on the board
SD_CD: J3.9 (SW_A), R14.2; also elsewhere on the board
SD_SEL: U15.1 (S), U16.1 (S); also elsewhere on the board

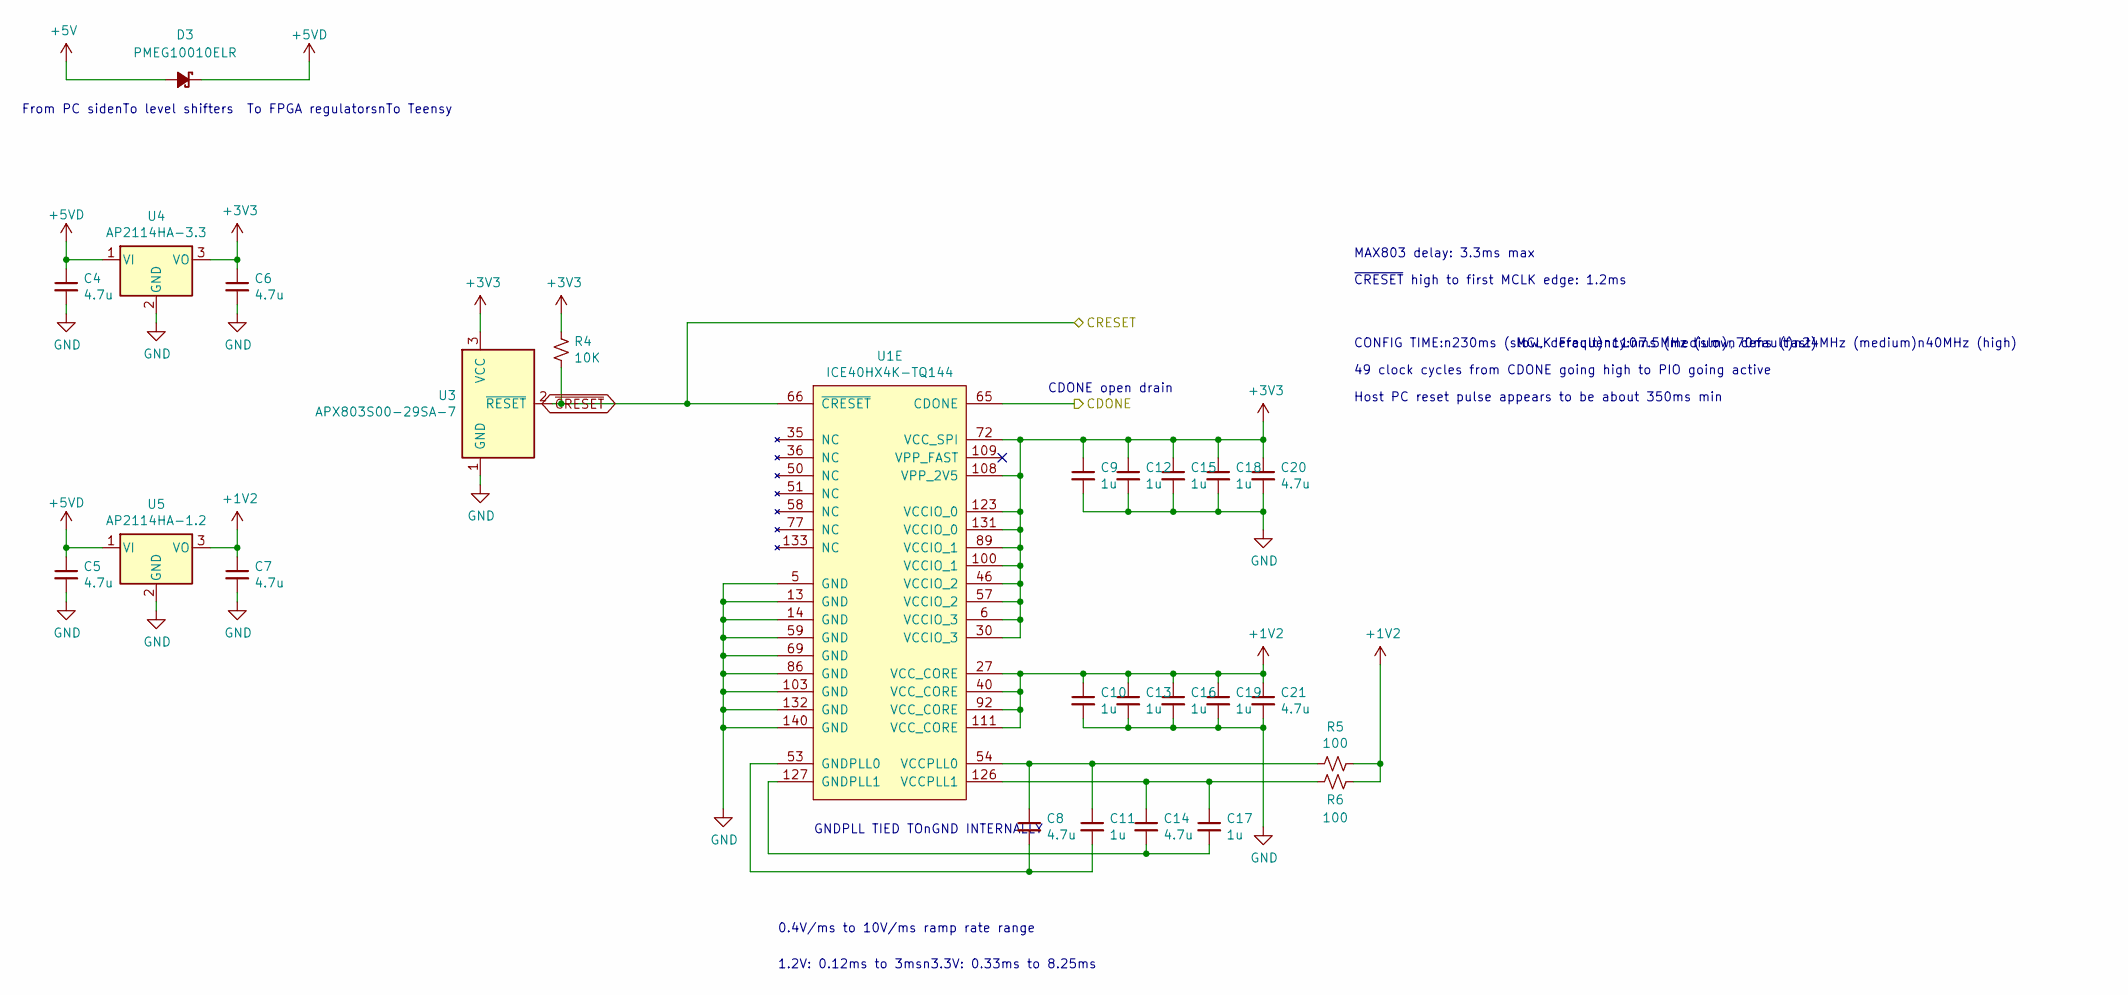
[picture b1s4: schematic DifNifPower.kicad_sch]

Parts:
C4, C5, C6, C7, C8, C14, C20, C21: 4.7u; CAPC1608X100; Mouser 187-CL10A475KP8NNNC
C9, C10, C11, C12, C13, C15, C16, C17, C18, C19: 1u; CAPC1608X100; Mouser 810-CGA3E1X7R1C105AC
D3: PMEG10010ELR; SOD3716X117; Mouser 771-PMEG10010ELRX
R4: 10K; RESC1608X55; Mouser 603-RC0603FR-0710KL
R5, R6: 100; RESC1608X55; Mouser 603-RC0603FR-07100RL
U1: ICE40HX4K-TQ144; TSQFP50P2200X2200X160-144; Mouser 842-ICE40HX4K-TQ144
U3: APX803S00-29SA-7; SOT95P230X117-3; Mouser 621-APX803S00-29SA-7
U4: AP2114HA-3.3; SOT230P700X170-3; Mouser 621-AP2114HA-3.3TRG1
U5: AP2114HA-1.2; SOT230P700X170-3; Mouser 621-AP2114HA-1.2TRG1

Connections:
+1V2: C7.1, C10.1, C13.1, C16.1, C19.1, C21.1, R5.1, R6.1, U1.27 (VCC_CORE), U1.40 (VCC_CORE), U1.92 (VCC_CORE), U1.111 (VCC_CORE), U5.3 (VO)
+3V3: C6.1, C9.1, C12.1, C15.1, C18.1, C20.1, R4.1, U1.6 (VCCIO_3), U1.30 (VCCIO_3), U1.46 (VCCIO_2), U1.57 (VCCIO_2), U1.72 (VCC_SPI), U1.89 (VCCIO_1), U1.100 (VCCIO_1), U1.108 (VPP_2V5), U1.123 (VCCIO_0), U1.131 (VCCIO_0), U3.3 (VCC), U4.3 (VO); also elsewhere on the board
+5V: D3.2 (A); also elsewhere on the board
+5VD: C4.1, C5.1, D3.1 (K), U4.1 (VI), U5.1 (VI); also elsewhere on the board
CDONE: U1.65 (CDONE); also elsewhere on the board
GND: C4.2, C5.2, C6.2, C7.2, C9.2, C10.2, C12.2, C13.2, C15.2, C16.2, C18.2, C19.2, C20.2, C21.2, U1.5 (GND), U1.13 (GND), U1.14 (GND), U1.59 (GND), U1.69 (GND), U1.86 (GND), U1.103 (GND), U1.132 (GND), U1.140 (GND), U3.1 (GND), U4.2 (GND), U5.2 (GND); also elsewhere on the board
unnamed: C8.2, C11.2, U1.53 (GNDPLL0)
unnamed: C14.2, C17.2, U1.127 (GNDPLL1)
unnamed: C8.1, C11.1, R5.2, U1.54 (VCCPLL0)
unnamed: C14.1, C17.1, R6.2, U1.126 (VCCPLL1)
~CRESET: R4.2, U1.66 (~CRESET), U3.2 (~RESET); also elsewhere on the board

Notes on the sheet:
49 clock cycles from CDONE going high to PIO going active
Host PC reset pulse appears to be about 350ms min
To FPGA regulatorsnTo Teensy
CONFIG TIME:n230ms (slow, default)n110ms (medium)n70ms (fast)
MCLK Frequency:n7.5MHz (slow, default)n24MHz (medium)n40MHz (high)
CDONE open drain
GNDPLL TIED TOnGND INTERNALLY
From PC sidenTo level shifters
0.4V/ms to 10V/ms ramp rate range
1.2V: 0.12ms to 3msn3.3V: 0.33ms to 8.25ms
~{CRESET} high to first MCLK edge: 1.2ms
MAX803 delay: 3.3ms max

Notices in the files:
pcb_finglonger/700CExtender.kicad_pcb:
© 2023 TUBE TIME
